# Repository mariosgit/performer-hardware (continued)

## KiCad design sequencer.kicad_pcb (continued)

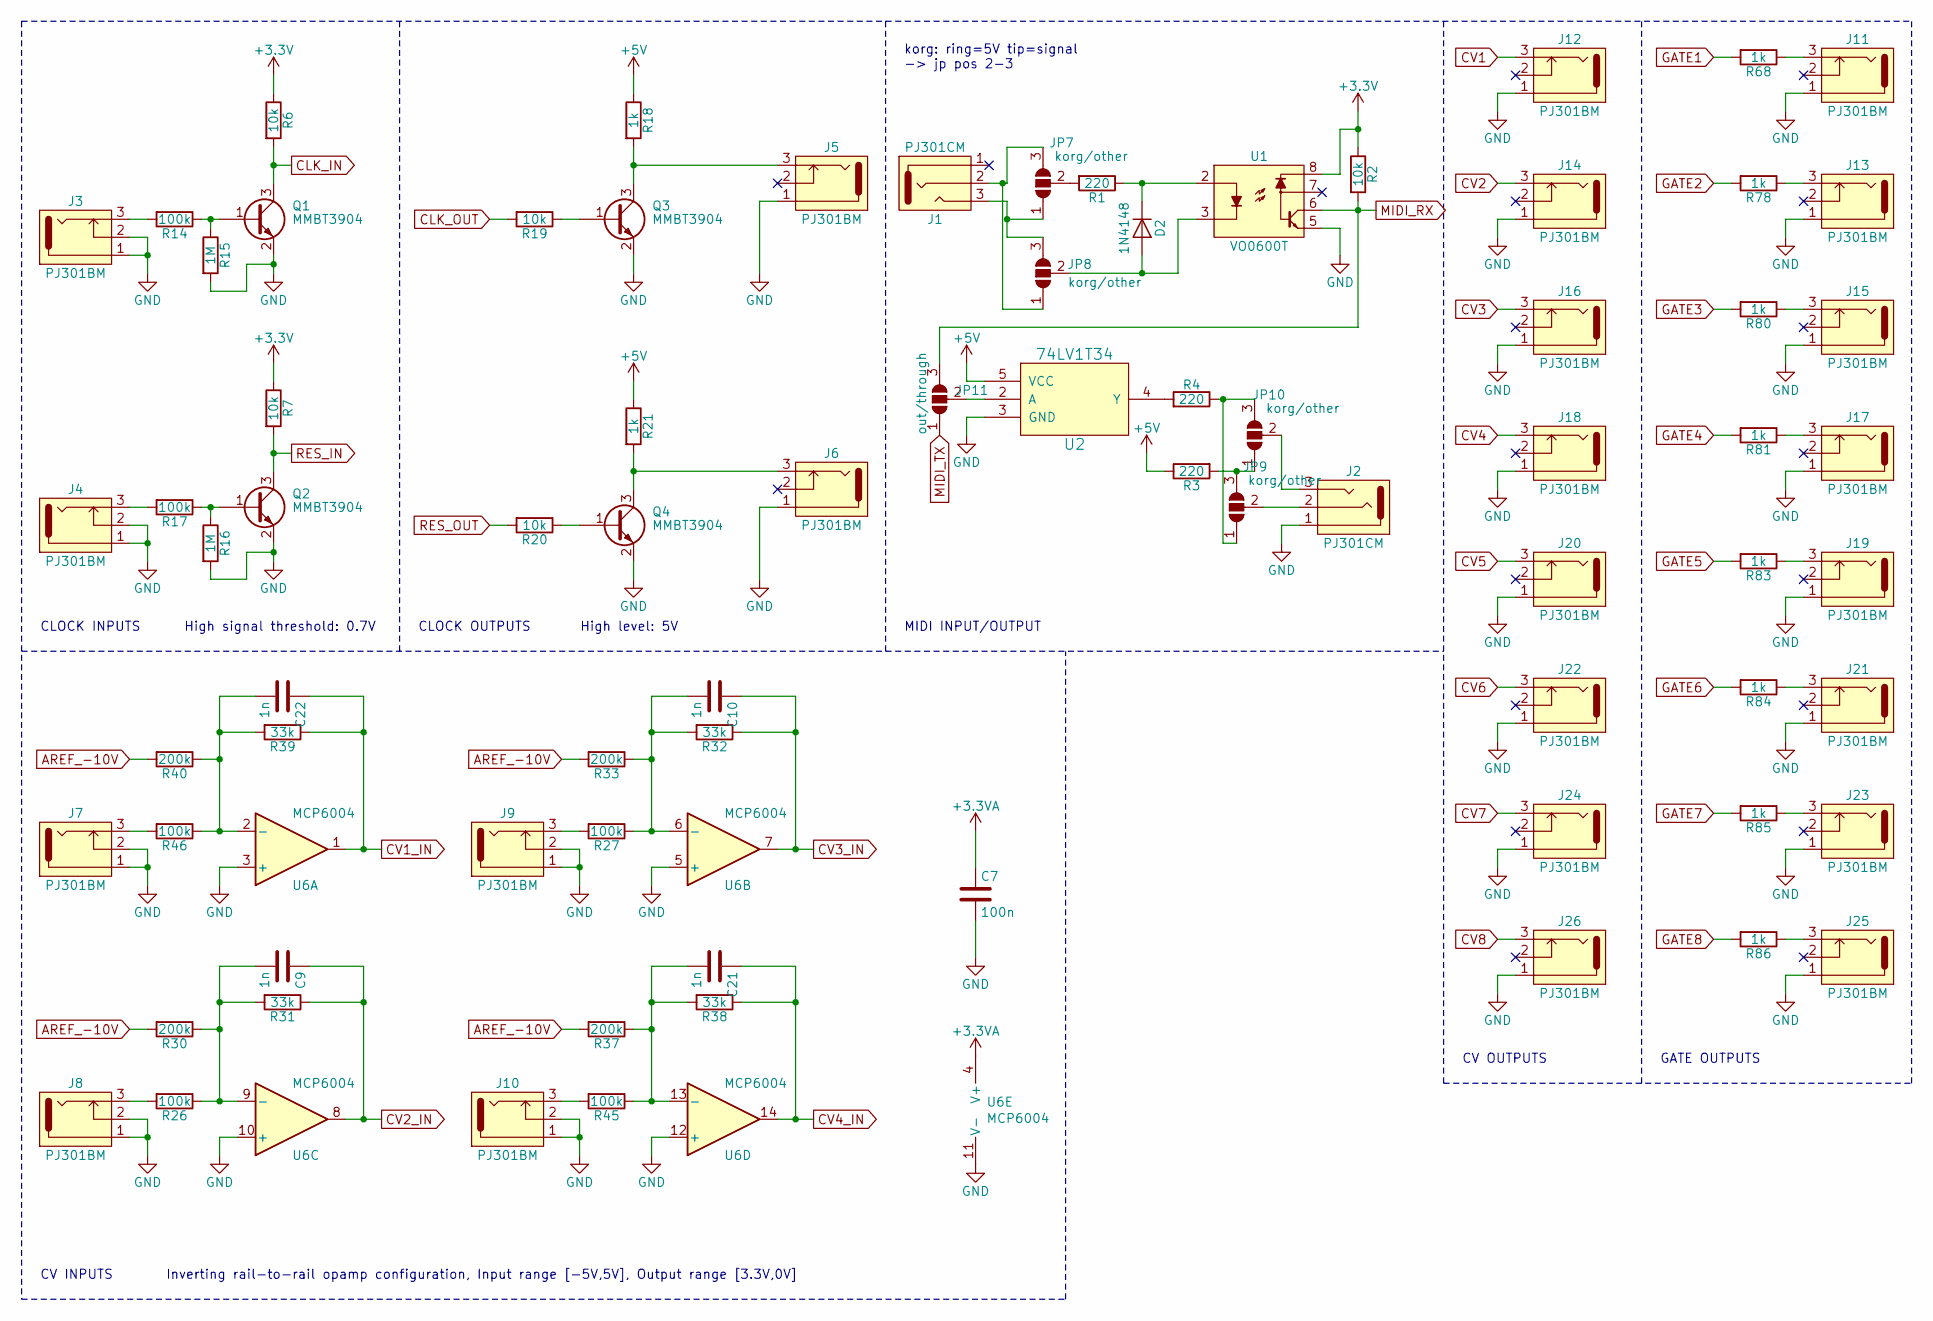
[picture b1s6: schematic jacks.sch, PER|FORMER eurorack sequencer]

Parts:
C7: 100n; C_0603
C9, C10, C21: 1n; C_0603
C22: 1n; C_0603; LCSC C1588
D2: 1N4148; D_SOD-123
J1, J2: PJ301CM; PJ301CM_OFFSET
J3, J4, J5, J6, J7, J8, J9, J10, J11, J12, J13, J14, J15, J16, J17, J18, J19, J20, J21, J22, J23, J24, J25, J26: PJ301BM
JP7, JP8, JP9, JP10: korg/other; SolderJumper-3_P1.3mm_Open_Pad1.0x1.5mm
JP11: out/through; SolderJumper-3_P1.3mm_Open_Pad1.0x1.5mm
Q1, Q2, Q3, Q4: MMBT3904; SOT-23
R1: 220; R_0603; LCSC C22962
R2, R6, R7, R19, R20: 10k; R_0603
R3, R4: 220; R_0603
R14, R17, R26, R27, R45, R46: 100k; R_0603
R15, R16: 1M; R_0603
R18, R21, R68, R78, R80, R81, R83, R84, R85, R86: 1k; R_0603
R30, R33, R37: 200k; R_0603
R31, R32, R38, R39: 33k; R_0603
R40: 200k; R_0603; LCSC C25811
U1: VO0600T; SOIC-8_3.9x4.9mm_P1.27mm
U2: 74LV1T34; SOT-23-5; LCSC C100024
U6: MCP6004; SOIC-14_3.9x8.7mm_P1.27mm; LCSC C7378

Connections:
+3.3VA: C7.1, U6.4 (V+); also elsewhere on the board
+5V: R3.1, R18.1, R21.1, U2.5 (VCC); also elsewhere on the board
AREF_-10V: R30.2, R33.2, R37.2, R40.2; also elsewhere on the board
CLK_IN: Q1.3 (C), R6.2; also elsewhere on the board
CLK_OUT: R19.2; also elsewhere on the board
CV1: J12.3; also elsewhere on the board
CV1_IN: C22.1, R39.1, U6.1; also elsewhere on the board
CV2: J14.3; also elsewhere on the board
CV2_IN: C9.1, R31.1, U6.8; also elsewhere on the board
CV3: J16.3; also elsewhere on the board
CV3_IN: C10.1, R32.1, U6.7; also elsewhere on the board
CV4: J18.3; also elsewhere on the board
CV4_IN: C21.1, R38.1, U6.14; also elsewhere on the board
CV5: J20.3; also elsewhere on the board
CV6: J22.3; also elsewhere on the board
CV7: J24.3; also elsewhere on the board
CV8: J26.3; also elsewhere on the board
GATE1: R68.2; also elsewhere on the board
GATE2: R78.2; also elsewhere on the board
GATE3: R80.2; also elsewhere on the board
GATE4: R81.2; also elsewhere on the board
GATE5: R83.2; also elsewhere on the board
GATE6: R84.2; also elsewhere on the board
GATE7: R85.2; also elsewhere on the board
GATE8: R86.2; also elsewhere on the board
GND: C7.2, J2.1, J3.1, J3.2, J4.1, J4.2, J5.1, J6.1, J7.1, J7.2, J8.1, J8.2, J9.1, J9.2, J10.1, J10.2, J11.1, J12.1, J13.1, J14.1, J15.1, J16.1, J17.1, J18.1, J19.1, J20.1, J21.1, J22.1, J23.1, J24.1, J25.1, J26.1, Q1.2 (E), Q2.2 (E), Q3.2 (E), Q4.2 (E), R15.2, R16.2, U1.5, U2.3 (GND), U6.3 (+), U6.5 (+), U6.10 (+), U6.11 (V-), U6.12 (+); also elsewhere on the board
MIDI_RX: JP11.3 (B), R2.2, U1.6; also elsewhere on the board
MIDI_TX: JP11.1 (A); also elsewhere on the board
unnamed: C9.2, R26.1, R30.1, R31.2, U6.9 (-)
unnamed: C10.2, R27.1, R32.2, R33.1, U6.6 (-)
unnamed: C21.2, R37.1, R38.2, R45.1, U6.13 (-)
unnamed: C22.2, R39.2, R40.1, R46.1, U6.2 (-)
unnamed: D2.1 (K), R1.1, U1.2
unnamed: D2.2 (A), JP8.2 (C), U1.3
unnamed: J1.2, JP7.3 (B), JP8.1 (A)
unnamed: J1.3, JP7.1 (A), JP8.3 (B)
unnamed: J2.2, JP9.2 (C)
unnamed: J2.3, JP10.2 (C)
unnamed: J3.3, R14.2
unnamed: J4.3, R17.2
unnamed: J5.3, Q3.3 (C), R18.2
unnamed: J6.3, Q4.3 (C), R21.2
unnamed: J7.3, R46.2
unnamed: J8.3, R26.2
unnamed: J9.3, R27.2
unnamed: J10.3, R45.2
unnamed: J11.3, R68.1
unnamed: J13.3, R78.1
unnamed: J15.3, R80.1
unnamed: J17.3, R81.1
unnamed: J19.3, R83.1
unnamed: J21.3, R84.1
unnamed: J23.3, R85.1
unnamed: J25.3, R86.1
unnamed: JP7.2 (C), R1.2
unnamed: JP9.3 (B), JP10.1 (A), R3.2
unnamed: JP9.1 (A), JP10.3 (B), R4.1
unnamed: JP11.2 (C), U2.2 (A)
unnamed: Q1.1 (B), R14.1, R15.1
unnamed: Q2.1 (B), R16.1, R17.1
unnamed: Q3.1 (B), R19.1
unnamed: Q4.1 (B), R20.1
unnamed: R4.2, U2.4 (Y)
RES_IN: Q2.3 (C), R7.2; also elsewhere on the board
RES_OUT: R20.2; also elsewhere on the board

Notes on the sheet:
CLOCK INPUTS
GATE OUTPUTS
CV OUTPUTS
MIDI INPUT/OUTPUT
CLOCK OUTPUTS
CV INPUTS
High signal threshold: 0.7V
High level: 5V
Inverting rail-to-rail opamp configuration, Input range [-5V,5V], Output range [3.3V,0V]
korg: ring=5V tip=signal -> jp pos 2-3

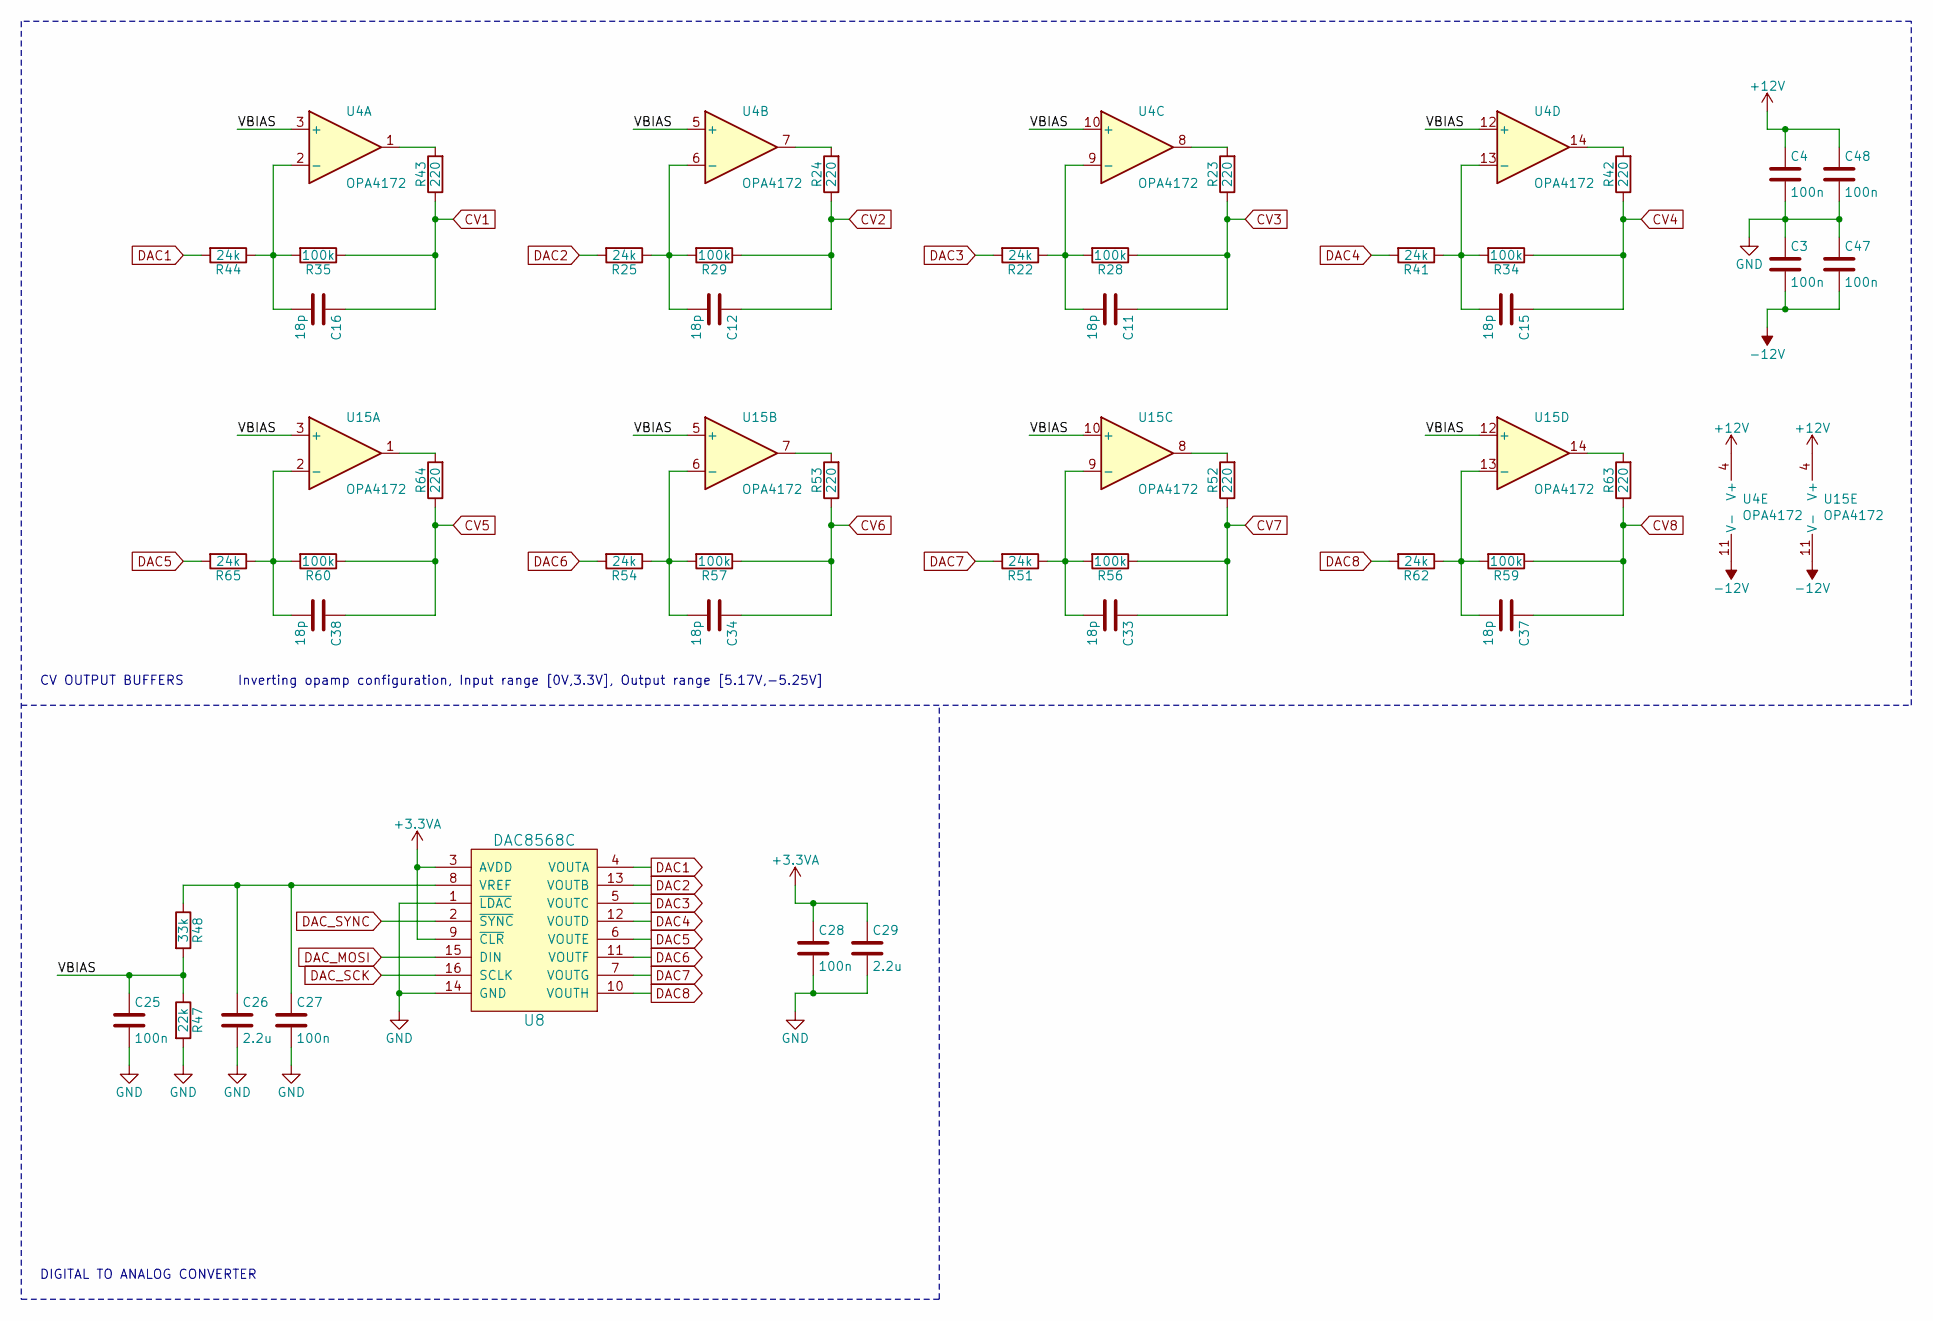
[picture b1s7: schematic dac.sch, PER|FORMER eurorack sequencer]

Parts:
C3, C4, C25, C27, C28, C47, C48: 100n; C_0603
C11, C12, C15, C16, C33, C34, C37, C38: 18p; C_0603
C26, C29: 2.2u; C_0805
R22, R25, R41, R51, R54, R62, R65: 24k; R_0603
R23, R24, R42, R43, R52, R53, R63, R64: 220; R_0603
R28, R29, R34, R35, R56, R57, R59, R60: 100k; R_0603
R44: 24k; R_0603; LCSC C23352
R47: 22k; R_0603; LCSC C31850
R48: 33k; R_0603
U4, U15: OPA4172; SOIC-14_3.9x8.7mm_P1.27mm
U8: DAC8568C; TSSOP-16_4.4x5mm_P0.65mm

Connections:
+3.3VA: C28.1, C29.1, U8.3 (AVDD), U8.9 (~CLR); also elsewhere on the board
+12V: C4.1, C48.1, U4.4 (V+), U15.4 (V+); also elsewhere on the board
-12V: C3.2, C47.2, U4.11 (V-), U15.11 (V-); also elsewhere on the board
/DAC/VBIAS: C25.1, R47.1, R48.2, U4.3 (+), U4.5 (+), U4.10 (+), U4.12 (+), U15.3 (+), U15.5 (+), U15.10 (+), U15.12 (+)
CV1: C16.1, R35.1, R43.1; also elsewhere on the board
CV2: C12.1, R24.1, R29.1; also elsewhere on the board
CV3: C11.1, R23.1, R28.1; also elsewhere on the board
CV4: C15.1, R34.1, R42.1; also elsewhere on the board
CV5: C38.1, R60.1, R64.1; also elsewhere on the board
CV6: C34.1, R53.1, R57.1; also elsewhere on the board
CV7: C33.1, R52.1, R56.1; also elsewhere on the board
CV8: C37.1, R59.1, R63.1; also elsewhere on the board
DAC1: R44.2, U8.4 (VOUTA)
DAC2: R25.2, U8.13 (VOUTB)
DAC3: R22.2, U8.5 (VOUTC)
DAC4: R41.2, U8.12 (VOUTD)
DAC5: R65.2, U8.6 (VOUTE)
DAC6: R54.2, U8.11 (VOUTF)
DAC7: R51.2, U8.7 (VOUTG)
DAC8: R62.2, U8.10 (VOUTH)
DAC_MOSI: U8.15 (DIN); also elsewhere on the board
DAC_SCK: U8.16 (SCLK); also elsewhere on the board
DAC_SYNC: U8.2 (~SYNC); also elsewhere on the board
GND: C3.1, C4.2, C25.2, C26.2, C27.2, C28.2, C29.2, C47.1, C48.2, R47.2, U8.1 (~LDAC), U8.14 (GND); also elsewhere on the board
unnamed: C11.2, R22.1, R28.2, U4.9 (-)
unnamed: C12.2, R25.1, R29.2, U4.6 (-)
unnamed: C15.2, R34.2, R41.1, U4.13 (-)
unnamed: C16.2, R35.2, R44.1, U4.2 (-)
unnamed: C26.1, C27.1, R48.1, U8.8 (VREF)
unnamed: C33.2, R51.1, R56.2, U15.9 (-)
unnamed: C34.2, R54.1, R57.2, U15.6 (-)
unnamed: C37.2, R59.2, R62.1, U15.13 (-)
unnamed: C38.2, R60.2, R65.1, U15.2 (-)
unnamed: R23.2, U4.8
unnamed: R24.2, U4.7
unnamed: R42.2, U4.14
unnamed: R43.2, U4.1
unnamed: R52.2, U15.8
unnamed: R53.2, U15.7
unnamed: R63.2, U15.14
unnamed: R64.2, U15.1

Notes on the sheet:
CV OUTPUT BUFFERS
DIGITAL TO ANALOG CONVERTER
Inverting opamp configuration, Input range [0V,3.3V], Output range [5.17V,-5.25V]

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
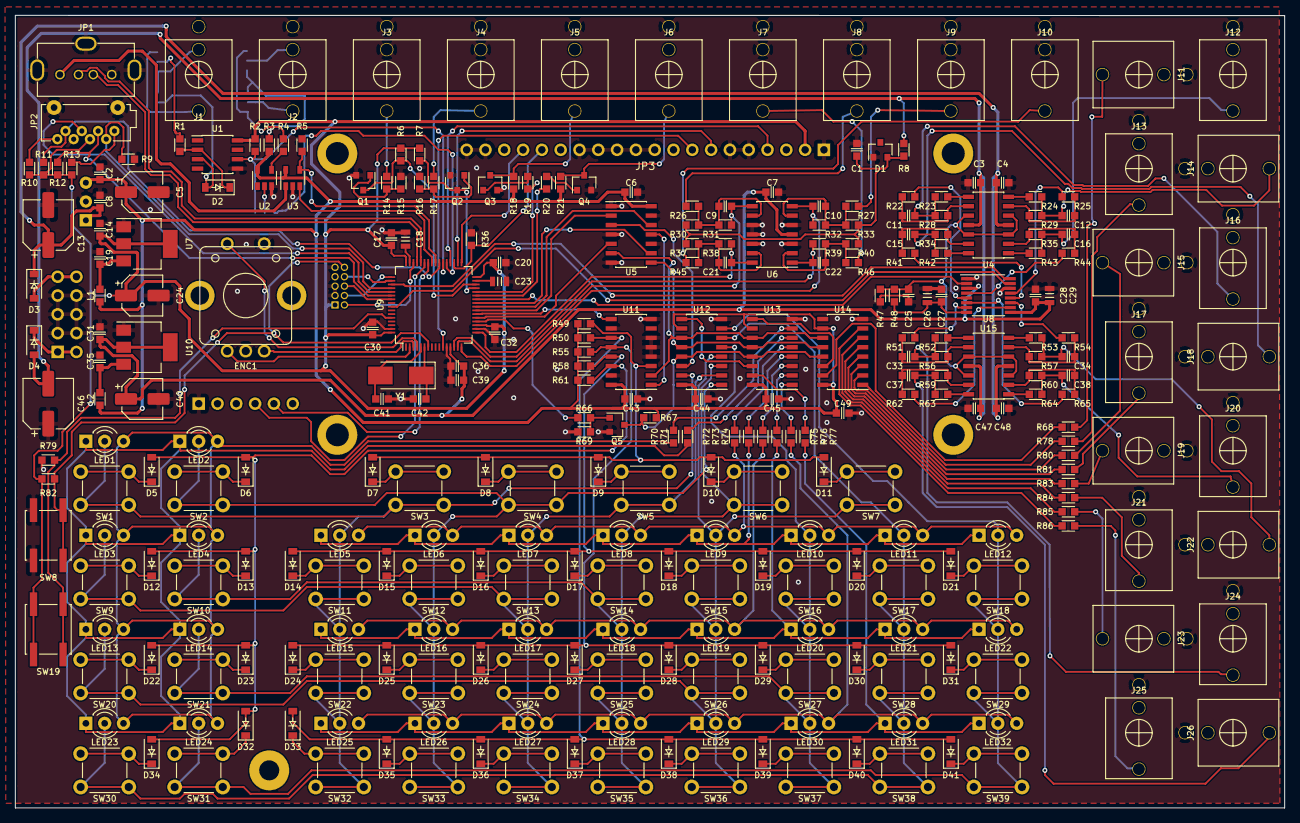
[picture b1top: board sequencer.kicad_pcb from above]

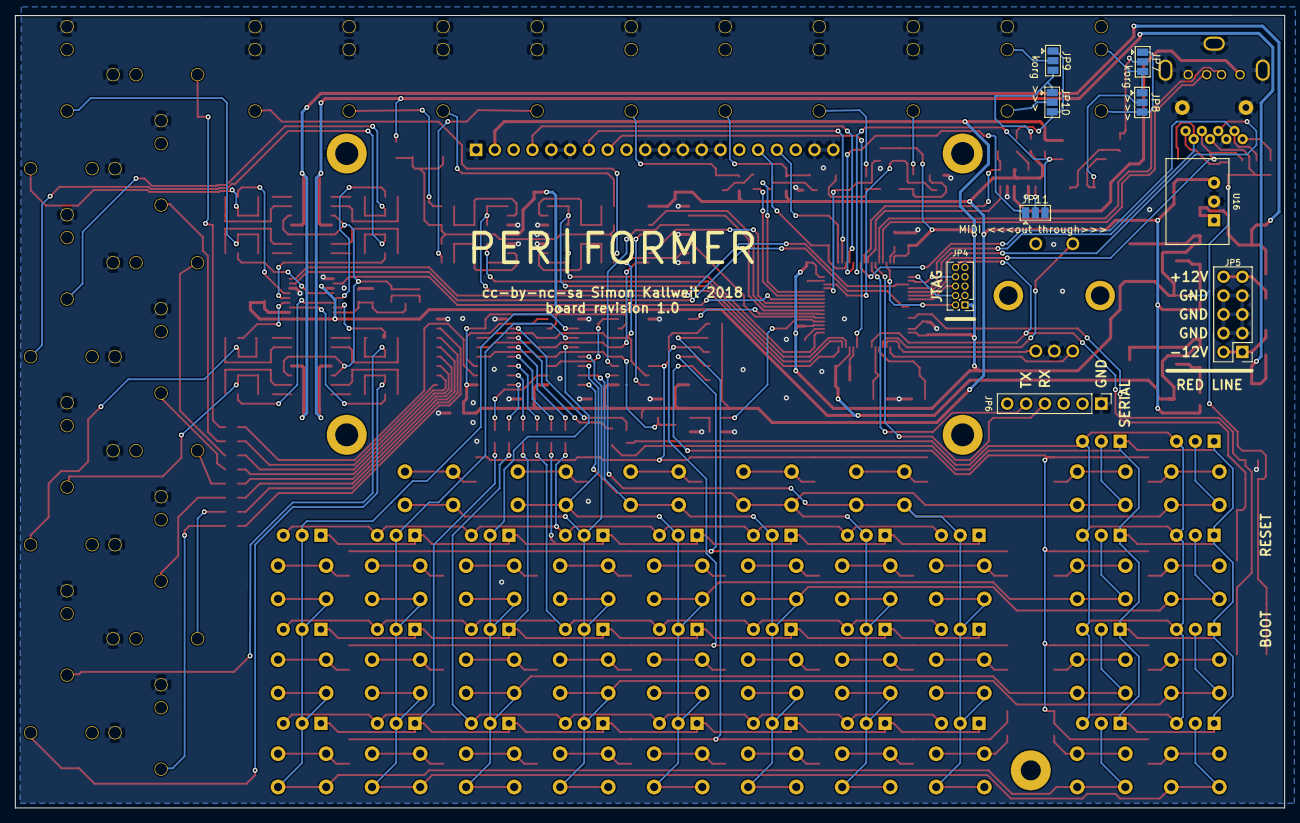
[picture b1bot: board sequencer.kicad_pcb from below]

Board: 2 copper layers, 171.4 x 107.1 mm, 309 parts (9 on the bottom side), 212 nets.

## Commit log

2020-06-18 Added JCLC part numbers.
2020-06-19 Added solder jumpers for midi polarity and midi out/through.
2020-06-19 Changed jack footprints to pj301cm.
2020-06-19 removed gerbers
2020-06-26 Fixed LCSC values.
2020-11-15 Some cleanup. Frontpanel with Copper Labels.

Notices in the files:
dac.sch:
cc-by-nc-sa
sequencer.kicad_pcb:
cc-by-nc-sa Simon Kallweit 2018
